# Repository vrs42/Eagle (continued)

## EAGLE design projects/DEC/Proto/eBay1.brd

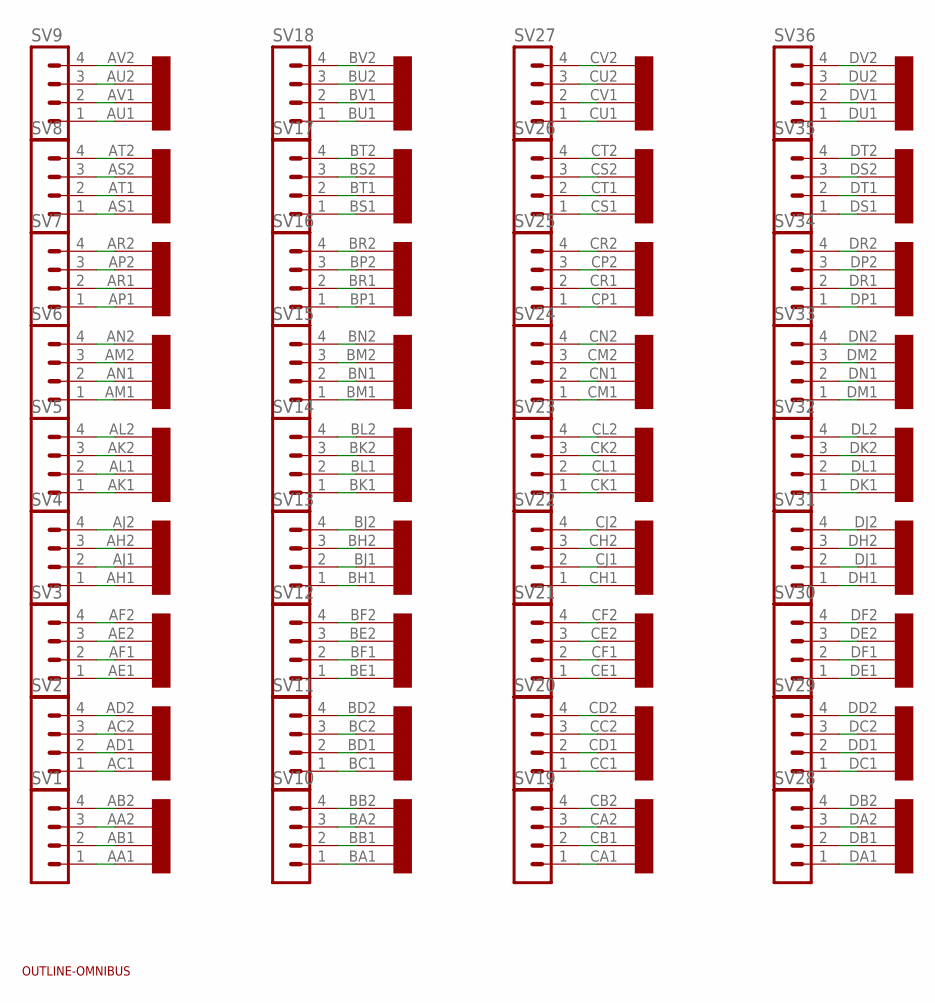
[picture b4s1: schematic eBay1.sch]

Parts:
SV1, SV2, SV3, SV4, SV5, SV6, SV7, SV8, SV9, SV10, SV11, SV12, SV13, SV14, SV15, SV16, SV17, SV18, SV19, SV20, SV21, SV22, SV23, SV24, SV25, SV26, SV27, SV28, SV29, SV30, SV31, SV32, SV33, SV34, SV35, SV36: MA04-1
U$1: OUTLINE-OMNIBUS; OMNIBUS
U$2: QUAD; EDGE-CON8

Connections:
unnamed: SV1.1, U$2.AA1
unnamed: SV1.2, U$2.AB1
unnamed: SV1.3, U$2.AA2
unnamed: SV1.4, U$2.AB2
unnamed: SV2.1, U$2.AC1
unnamed: SV2.2, U$2.AD1
unnamed: SV2.3, U$2.AC2
unnamed: SV2.4, U$2.AD2
unnamed: SV3.1, U$2.AE1
unnamed: SV3.2, U$2.AF1
unnamed: SV4.1, U$2.AH1
unnamed: SV4.2, U$2.AJ1
unnamed: SV5.1, U$2.AK1
unnamed: SV5.2, U$2.AL1
unnamed: SV6.1, U$2.AM1
unnamed: SV6.2, U$2.AN1
unnamed: SV7.1, U$2.AP1
unnamed: SV7.2, U$2.AR1
unnamed: SV8.1, U$2.AS1
unnamed: SV8.2, U$2.AT1
unnamed: SV9.1, U$2.AU1
unnamed: SV9.2, U$2.AV1
unnamed: SV3.3, U$2.AE2
unnamed: SV3.4, U$2.AF2
unnamed: SV4.3, U$2.AH2
unnamed: SV4.4, U$2.AJ2
unnamed: SV5.3, U$2.AK2
unnamed: SV5.4, U$2.AL2
unnamed: SV6.3, U$2.AM2
unnamed: SV6.4, U$2.AN2
unnamed: SV7.3, U$2.AP2
unnamed: SV7.4, U$2.AR2
unnamed: SV8.3, U$2.AS2
unnamed: SV8.4, U$2.AT2
unnamed: SV9.3, U$2.AU2
unnamed: SV9.4, U$2.AV2
unnamed: SV10.1, U$2.BA1
unnamed: SV10.2, U$2.BB1
unnamed: SV11.1, U$2.BC1
unnamed: SV11.2, U$2.BD1
unnamed: SV12.1, U$2.BE1
unnamed: SV12.2, U$2.BF1
unnamed: SV13.1, U$2.BH1
unnamed: SV13.2, U$2.BJ1
unnamed: SV14.1, U$2.BK1
unnamed: SV14.2, U$2.BL1
unnamed: SV15.1, U$2.BM1
unnamed: SV15.2, U$2.BN1
unnamed: SV16.1, U$2.BP1
unnamed: SV16.2, U$2.BR1
unnamed: SV17.1, U$2.BS1
unnamed: SV17.2, U$2.BT1
unnamed: SV18.1, U$2.BU1
unnamed: SV18.2, U$2.BV1
unnamed: SV10.3, U$2.BA2
unnamed: SV10.4, U$2.BB2
unnamed: SV11.3, U$2.BC2
unnamed: SV11.4, U$2.BD2
unnamed: SV12.3, U$2.BE2
unnamed: SV12.4, U$2.BF2
unnamed: SV13.3, U$2.BH2
unnamed: SV13.4, U$2.BJ2
unnamed: SV14.3, U$2.BK2
unnamed: SV14.4, U$2.BL2
unnamed: SV15.3, U$2.BM2
unnamed: SV15.4, U$2.BN2
unnamed: SV16.3, U$2.BP2
unnamed: SV16.4, U$2.BR2
unnamed: SV18.4, U$2.BV2
unnamed: SV18.3, U$2.BU2
unnamed: SV17.4, U$2.BT2
unnamed: SV17.3, U$2.BS2
unnamed: SV19.1, U$2.CA1
unnamed: SV19.2, U$2.CB1
unnamed: SV20.1, U$2.CC1
unnamed: SV20.2, U$2.CD1
unnamed: SV21.1, U$2.CE1
unnamed: SV21.2, U$2.CF1
unnamed: SV22.1, U$2.CH1
unnamed: SV22.2, U$2.CJ1
unnamed: SV19.3, U$2.CA2
unnamed: SV19.4, U$2.CB2
unnamed: SV20.3, U$2.CC2
unnamed: SV20.4, U$2.CD2
unnamed: SV21.3, U$2.CE2
unnamed: SV21.4, U$2.CF2
unnamed: SV22.3, U$2.CH2
unnamed: SV22.4, U$2.CJ2
unnamed: SV23.1, U$2.CK1
unnamed: SV23.2, U$2.CL1
unnamed: SV24.1, U$2.CM1
unnamed: SV24.2, U$2.CN1
unnamed: SV25.1, U$2.CP1
unnamed: SV25.2, U$2.CR1
unnamed: SV26.1, U$2.CS1
unnamed: SV26.2, U$2.CT1
unnamed: SV27.1, U$2.CU1
unnamed: SV27.2, U$2.CV1
unnamed: SV23.3, U$2.CK2
unnamed: SV23.4, U$2.CL2
unnamed: SV24.3, U$2.CM2
unnamed: SV24.4, U$2.CN2
unnamed: SV25.3, U$2.CP2
unnamed: SV25.4, U$2.CR2
unnamed: SV26.3, U$2.CS2
unnamed: SV26.4, U$2.CT2
unnamed: SV27.3, U$2.CU2
unnamed: SV27.4, U$2.CV2
unnamed: SV28.1, U$2.DA1
unnamed: SV28.2, U$2.DB1
unnamed: SV29.1, U$2.DC1
unnamed: SV29.2, U$2.DD1
unnamed: SV30.1, U$2.DE1
unnamed: SV30.2, U$2.DF1
unnamed: SV31.1, U$2.DH1
unnamed: SV31.2, U$2.DJ1
unnamed: SV32.1, U$2.DK1
unnamed: SV32.2, U$2.DL1
unnamed: SV33.1, U$2.DM1
unnamed: SV33.2, U$2.DN1
unnamed: SV34.1, U$2.DP1
unnamed: SV34.2, U$2.DR1
unnamed: SV35.1, U$2.DS1
unnamed: SV35.2, U$2.DT1
unnamed: SV36.1, U$2.DU1
unnamed: SV36.2, U$2.DV1
unnamed: SV36.4, U$2.DV2
unnamed: SV36.3, U$2.DU2
unnamed: SV35.4, U$2.DT2
unnamed: SV35.3, U$2.DS2
unnamed: SV34.4, U$2.DR2
unnamed: SV34.3, U$2.DP2
unnamed: SV28.3, U$2.DA2
unnamed: SV28.4, U$2.DB2
unnamed: SV29.3, U$2.DC2
unnamed: SV29.4, U$2.DD2
unnamed: SV30.3, U$2.DE2
unnamed: SV30.4, U$2.DF2
unnamed: SV31.3, U$2.DH2
unnamed: SV31.4, U$2.DJ2
unnamed: SV32.3, U$2.DK2
unnamed: SV32.4, U$2.DL2
unnamed: SV33.3, U$2.DM2
unnamed: SV33.4, U$2.DN2

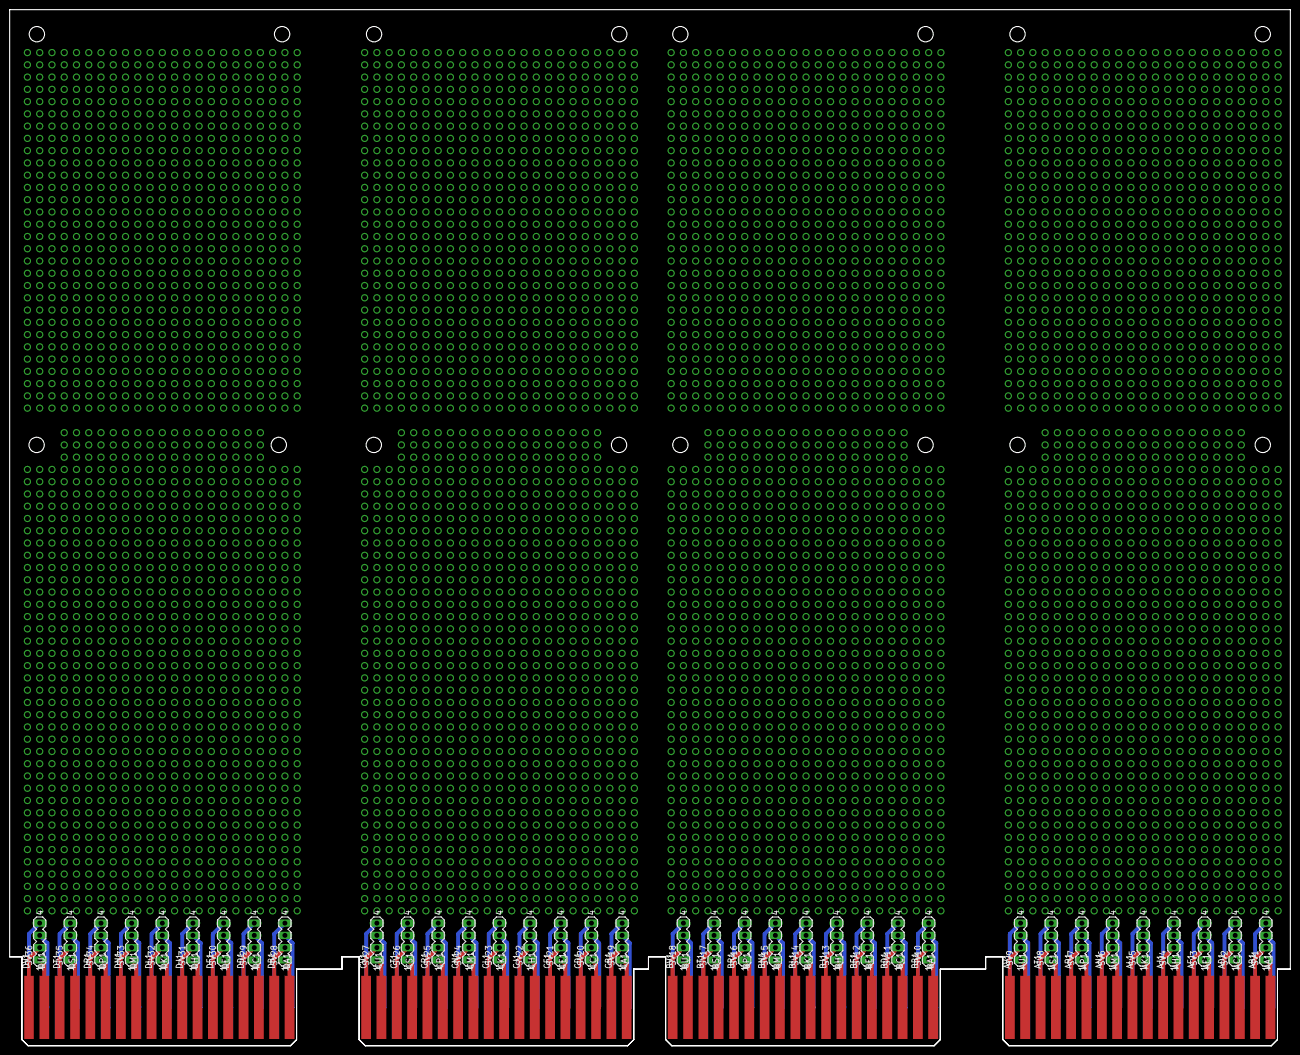
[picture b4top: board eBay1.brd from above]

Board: 2 copper layers, 265.3 x 214.6 mm, 38 parts (0 on the bottom side), 144 nets.

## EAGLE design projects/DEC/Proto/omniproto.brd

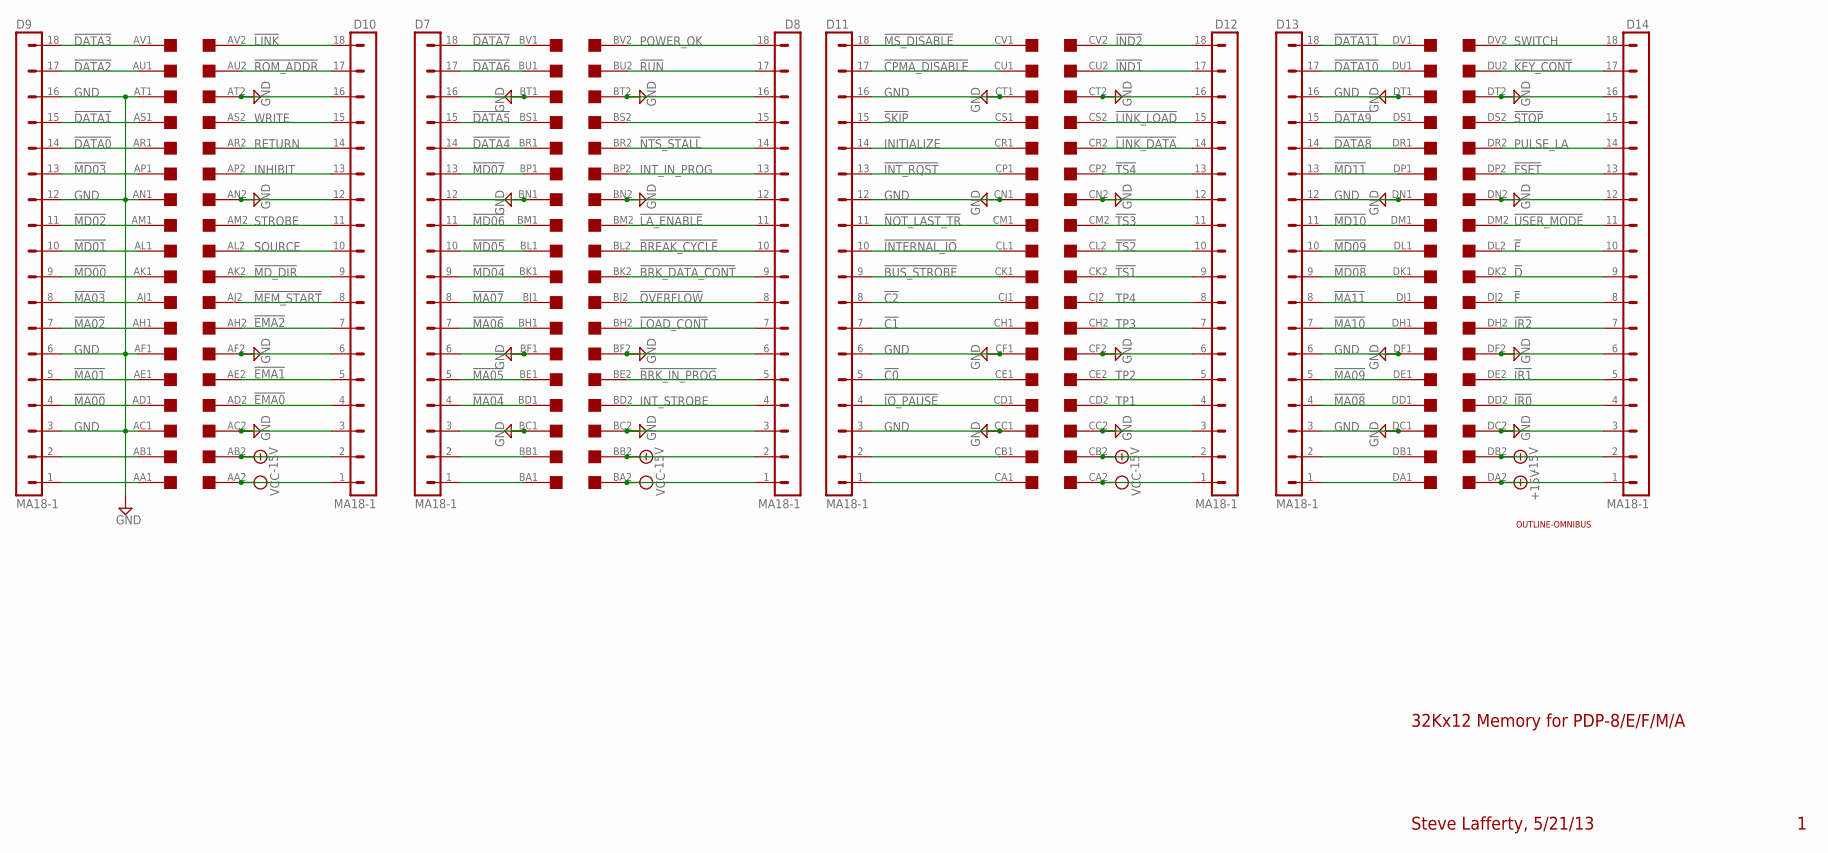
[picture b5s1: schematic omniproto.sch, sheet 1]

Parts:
D7, D8, D9, D10, D11, D12, D13, D14: MA18-1
U$1: OUTLINE-OMNIBUS; OMNIBUS
U$2: QUAD; EDGE-CON8

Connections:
!BREAK_CYCLE: D8.10, U$2.BL2
!BRK_DATA_CONT: D8.9, U$2.BK2
!BRK_IN_PROG: D8.5, U$2.BE2
!BUS_STROBE: D11.9, U$2.CK1
!C0: D11.5, U$2.CE1
!C1: D11.7, U$2.CH1
!C2: D11.8, U$2.CJ1
!CPMA_DISABLE: D11.17, U$2.CU1
!D: D14.9, U$2.DK2
!DATA0: D9.14, U$2.AR1
!DATA1: D9.15, U$2.AS1
!DATA2: D9.17, U$2.AU1
!DATA3: D9.18, U$2.AV1
!DATA4: D7.14, U$2.BR1
!DATA5: D7.15, U$2.BS1
!DATA6: D7.17, U$2.BU1
!DATA7: D7.18, U$2.BV1
!DATA8: D13.14, U$2.DR1
!DATA9: D13.15, U$2.DS1
!DATA10: D13.17, U$2.DU1
!DATA11: D13.18, U$2.DV1
!E: D14.10, U$2.DL2
!EMA0: D10.4, U$2.AD2
!EMA1: D10.5, U$2.AE2
!EMA2: D10.7, U$2.AH2
!F: D14.8, U$2.DJ2
!FSET: D14.13, U$2.DP2
!IND1: D12.17, U$2.CU2
!IND2: D12.18, U$2.CV2
!INTERNAL_IO: D11.10, U$2.CL1
!INT_RQST: D11.13, U$2.CP1
!IO_PAUSE: D11.4, U$2.CD1
!IR0: D14.4, U$2.DD2
!IR1: D14.5, U$2.DE2
!IR2: D14.7, U$2.DH2
!KEY_CONT: D14.17, U$2.DU2
!LA_ENABLE: D8.11, U$2.BM2
!LINK: D10.18, U$2.AV2
!LINK_DATA: D12.14, U$2.CR2
!LINK_LOAD: D12.15, U$2.CS2
!LOAD_CONT: D8.7, U$2.BH2
!MA00: D9.4, U$2.AD1
!MA01: D9.5, U$2.AE1
!MA02: D9.7, U$2.AH1
!MA03: D9.8, U$2.AJ1
!MA04: D7.4, U$2.BD1
!MA05: D7.5, U$2.BE1
!MA06: D7.7, U$2.BH1
!MA07: D7.8, U$2.BJ1
!MA08: D13.4, U$2.DD1
!MA09: D13.5, U$2.DE1
!MA10: D13.7, U$2.DH1
!MA11: D13.8, U$2.DJ1
!MD00: D9.9, U$2.AK1
!MD01: D9.10, U$2.AL1
!MD02: D9.11, U$2.AM1
!MD03: D9.13, U$2.AP1
!MD04: D7.9, U$2.BK1
!MD05: D7.10, U$2.BL1
!MD06: D7.11, U$2.BM1
!MD07: D7.13, U$2.BP1
!MD08: D13.9, U$2.DK1
!MD09: D13.10, U$2.DL1
!MD10: D13.11, U$2.DM1
!MD11: D13.13, U$2.DP1
!MD_DIR: D10.9, U$2.AK2
!MEM_START: D10.8, U$2.AJ2
!MS_DISABLE: D11.18, U$2.CV1
!NOT_LAST_TR: D11.11, U$2.CM1
!NTS_STALL: D8.14, U$2.BR2
!OVERFLOW: D8.8, U$2.BJ2
!ROM_ADDR: D10.17, U$2.AU2
!RUN: D8.17, U$2.BU2
!SKIP: D11.15, U$2.CS1
!STOP: D14.15, U$2.DS2
!TS1: D12.9, U$2.CK2
!TS2: D12.10, U$2.CL2
!TS3: D12.11, U$2.CM2
!TS4: D12.13, U$2.CP2
!USER_MODE: D14.11, U$2.DM2
+15V: D14.1, U$2.DA2
-15V: D8.2, D10.2, D12.2, D14.2, U$2.AB2, U$2.BB2, U$2.CB2, U$2.DB2
GND: D7.3, D7.6, D7.12, D7.16, D8.3, D8.6, D8.12, D8.16, D9.3, D9.6, D9.12, D9.16, D10.3, D10.6, D10.12, D10.16, D11.3, D11.6, D11.12, D11.16, D12.3, D12.6, D12.12, D12.16, D13.3, D13.6, D13.12, D13.16, D14.3, D14.6, D14.12, D14.16, U$2.AC1, U$2.AC2, U$2.AF1, U$2.AF2, U$2.AN1, U$2.AN2, U$2.AT1, U$2.AT2, U$2.BC1, U$2.BC2, U$2.BF1, U$2.BF2, U$2.BN1, U$2.BN2, U$2.BT1, U$2.BT2, U$2.CC1, U$2.CC2, U$2.CF1, U$2.CF2, U$2.CN1, U$2.CN2, U$2.CT1, U$2.CT2, U$2.DC1, U$2.DC2, U$2.DF1, U$2.DF2, U$2.DN1, U$2.DN2, U$2.DT1, U$2.DT2; also elsewhere on the board
INHIBIT: D10.13, U$2.AP2
INITIALIZE: D11.14, U$2.CR1
INT_IN_PROG: D8.13, U$2.BP2
INT_STROBE: D8.4, U$2.BD2
unnamed: D9.2, U$2.AB1
unnamed: D9.1, U$2.AA1
unnamed: D7.2, U$2.BB1
unnamed: D7.1, U$2.BA1
unnamed: D11.1, U$2.CA1
unnamed: D8.15, U$2.BS2
unnamed: D11.2, U$2.CB1
unnamed: D13.1, U$2.DA1
unnamed: D13.2, U$2.DB1
POWER_OK: D8.18, U$2.BV2
PULSE_LA: D14.14, U$2.DR2
RETURN: D10.14, U$2.AR2
SOURCE: D10.10, U$2.AL2
STROBE: D10.11, U$2.AM2
SWITCH: D14.18, U$2.DV2
TP1: D12.4, U$2.CD2
TP2: D12.5, U$2.CE2
TP3: D12.7, U$2.CH2
TP4: D12.8, U$2.CJ2
VCC: D8.1, D10.1, D12.1, U$2.AA2, U$2.BA2, U$2.CA2; also elsewhere on the board
WRITE: D10.15, U$2.AS2

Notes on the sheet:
32Kx12 Memory for PDP-8/E/F/M/A
Steve Lafferty, 5/21/13
